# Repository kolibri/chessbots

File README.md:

# Chessbots

## What is this about?

You probably have seen something like this:

My idea is, to make the pieces movable. You play a game on your mobile phone or any other device that has a webbrowser, and the real pieces on the street will also make every move you and your opponent will make.

So, we are talking about 32 individual robots, each one is a selfmoving chesspiece, that play our game.

## Concept, Idea

Each piece is build with a ESP32-CAM board with two wheel attached, camera facing down. So we talk about a robot, that takes a picture of what is under it.
Hopefully, this is the board, that we play on. Because, this will have special markings, that help us to determine the position of the bot and where it is heading at.
Because, if we know that, we can check all the positions against an ongoing chess game, and so on.
This is the first main goals: Make the bots recognize its position and make it able to move to another position.

This is a very early project state. And it is slow moving. 

You may contact me (have a look at my github profile, or leave an issue), if you are interested in this project or want to contribute. There are plenty of issues, that are not solved yet. (languages I understand: german and english)

## Languages

Python (Flask), Micropython, ReactJs for Debug Frontend

Docker for dev env

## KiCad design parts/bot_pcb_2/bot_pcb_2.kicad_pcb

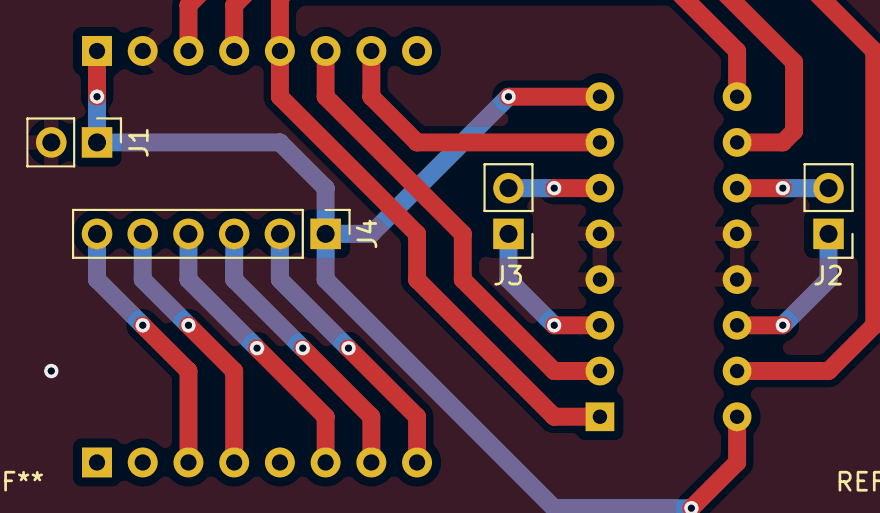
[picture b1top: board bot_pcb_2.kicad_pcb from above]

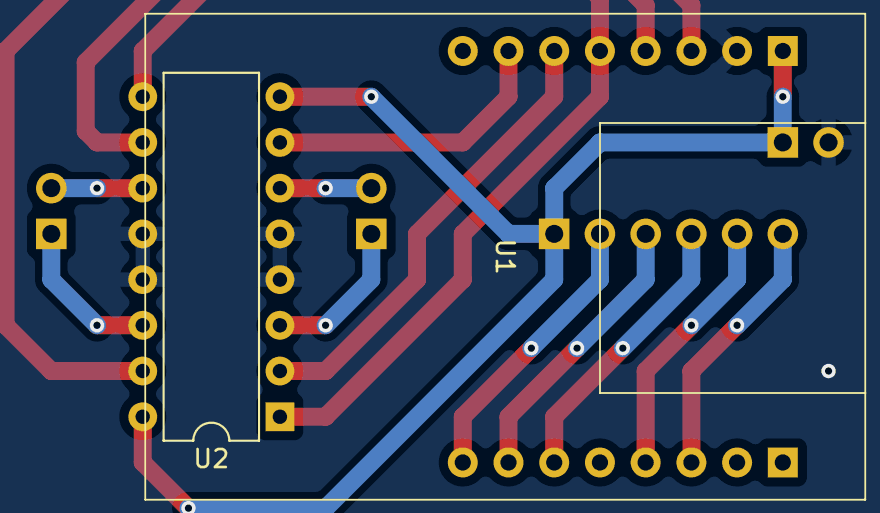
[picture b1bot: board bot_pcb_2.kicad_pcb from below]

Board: 2 copper layers, 6 parts (2 on the bottom side), 16 nets.

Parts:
J1, J2, J3: Conn_01x02_Pin; PinHeader_1x02_P2.54mm_Vertical
J4: Conn_01x06; PinHeader_1x06_P2.54mm_Vertical
U1: ESP32-CAM
U2: L293D; DIP-16_W7.62mm

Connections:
unnamed: J1.1, J4.1, U1.8 (5V), U2.8 (VCC2), U2.16 (VCC1)
unnamed: J1.2, U1.7 (GND_1), U2.4 (GND), U2.5 (GND), U2.12 (GND), U2.13 (GND)
unnamed: J2.1, U2.14 (4Y)
unnamed: J2.2, U2.11 (3Y)
unnamed: J3.1, U2.3 (1Y)
unnamed: J3.2, U2.6 (2Y)
unnamed: J4.2, U1.16 (GND_3)
unnamed: J4.3, U1.15 (U0T)
unnamed: J4.4, U1.14 (U0R)
unnamed: J4.5, U1.12 (GND_2)
unnamed: J4.6, U1.11 (IO0)
unnamed: U1.2 (IO2), U2.7 (2A)
unnamed: U1.6 (IO12), U2.15 (4A)
unnamed: U1.5 (IO13), U2.10 (3A)
unnamed: U1.3 (IO14), U2.2 (1A)
unnamed: U1.4 (IO15), U2.1 (EN1,2), U2.9 (EN3,4)

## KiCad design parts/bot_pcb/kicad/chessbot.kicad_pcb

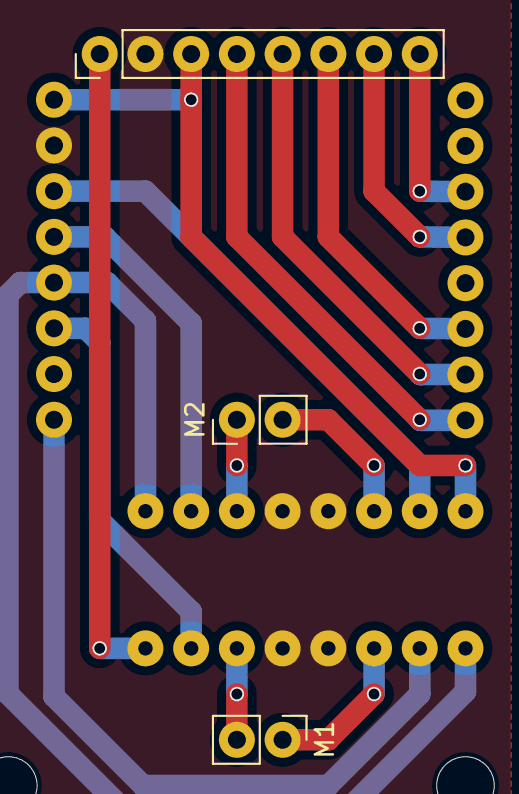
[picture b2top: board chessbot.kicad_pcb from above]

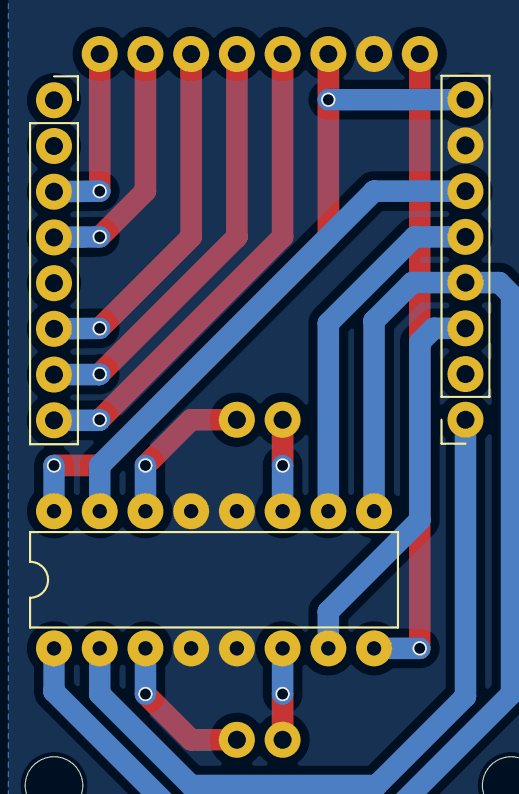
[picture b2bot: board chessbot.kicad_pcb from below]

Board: 2 copper layers, 10 parts (3 on the bottom side), 17 nets.

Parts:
Conn_ESP1, Conn_ESP2: Conn_01x08_Socket; PinSocket_1x08_P2.54mm_Vertical
H1, H2, H3, H4: MountingHole; MountingHole_3.2mm_M3
L293D1: L293D; DIP-16_W7.62mm
M1, M2: Conn_01x02_Pin; PinHeader_1x02_P2.54mm_Vertical
VCC_Flash1: Conn_01x08_Pin; PinHeader_1x08_P2.54mm_Vertical

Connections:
GND: Conn_ESP2.7, L293D1.4 (GND), L293D1.5 (GND), L293D1.12 (GND), L293D1.13 (GND), VCC_Flash1.2
unnamed: Conn_ESP2.8, L293D1.16 (VCC1), VCC_Flash1.3
unnamed: L293D1.8 (VCC2), VCC_Flash1.1
unnamed: Conn_ESP1.3, VCC_Flash1.8
unnamed: Conn_ESP1.4, VCC_Flash1.7
unnamed: Conn_ESP1.6, VCC_Flash1.6
unnamed: Conn_ESP1.7, VCC_Flash1.5
unnamed: Conn_ESP1.8, VCC_Flash1.4
unnamed: Conn_ESP2.1, L293D1.2 (1A)
unnamed: Conn_ESP2.3, L293D1.7 (2A)
unnamed: Conn_ESP2.4, L293D1.1 (EN1,2), L293D1.9 (EN3,4)
unnamed: Conn_ESP2.5, L293D1.10 (3A)
unnamed: Conn_ESP2.6, L293D1.15 (4A)
unnamed: L293D1.3 (1Y), M1.1
unnamed: L293D1.6 (2Y), M1.2
unnamed: L293D1.11 (3Y), M2.1
unnamed: L293D1.14 (4Y), M2.2

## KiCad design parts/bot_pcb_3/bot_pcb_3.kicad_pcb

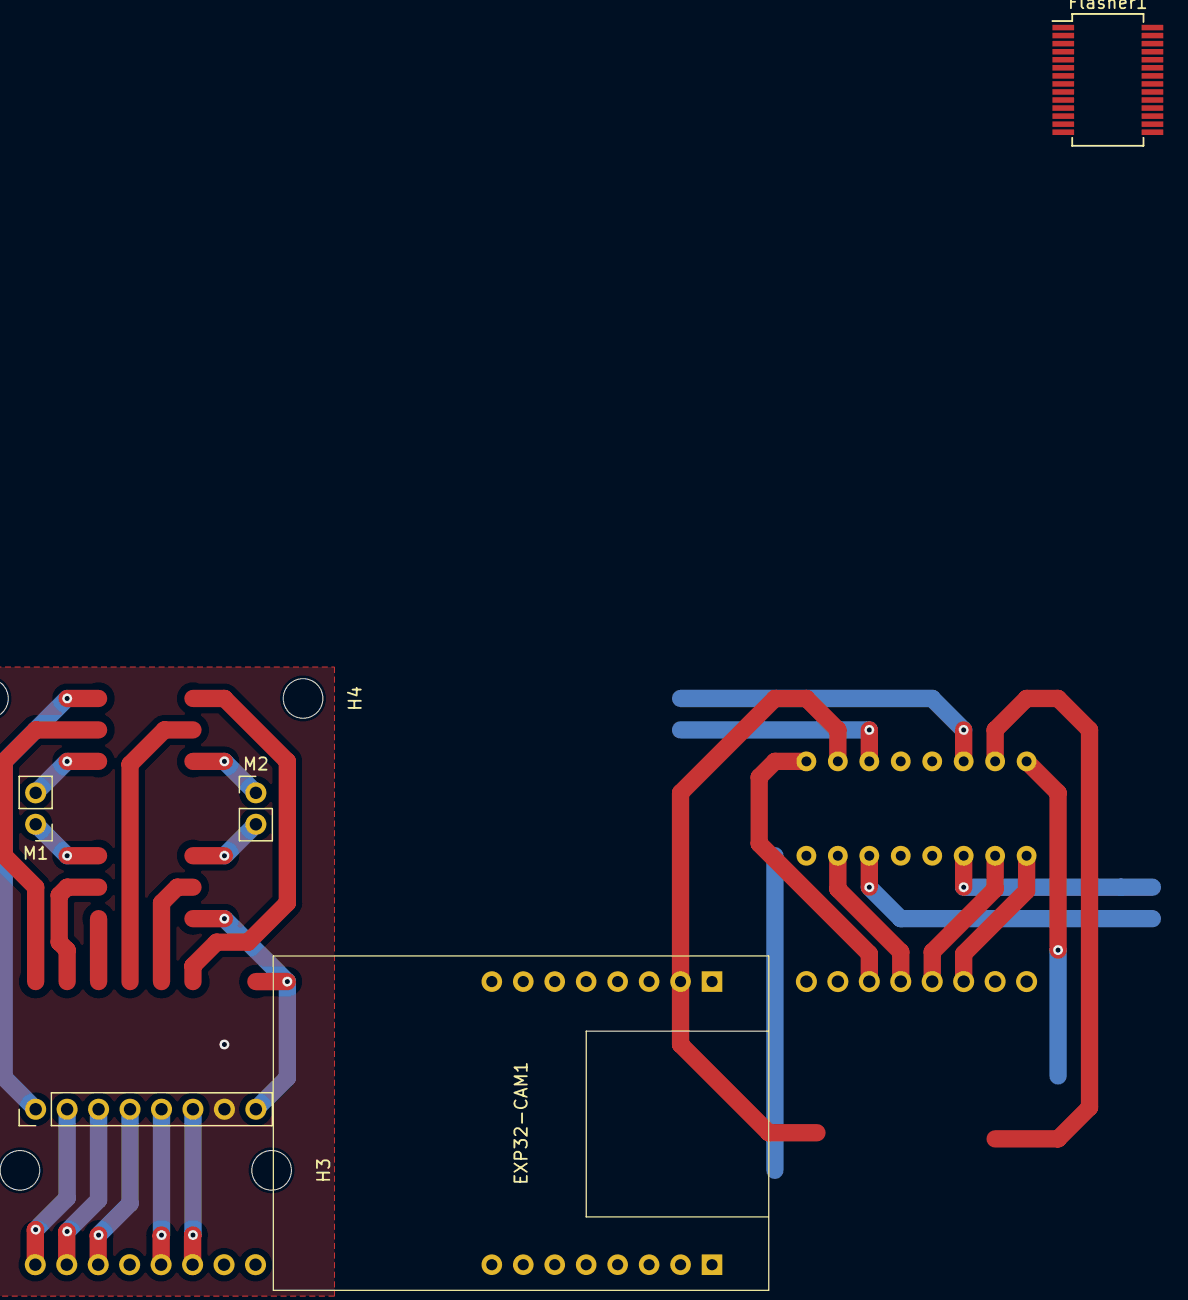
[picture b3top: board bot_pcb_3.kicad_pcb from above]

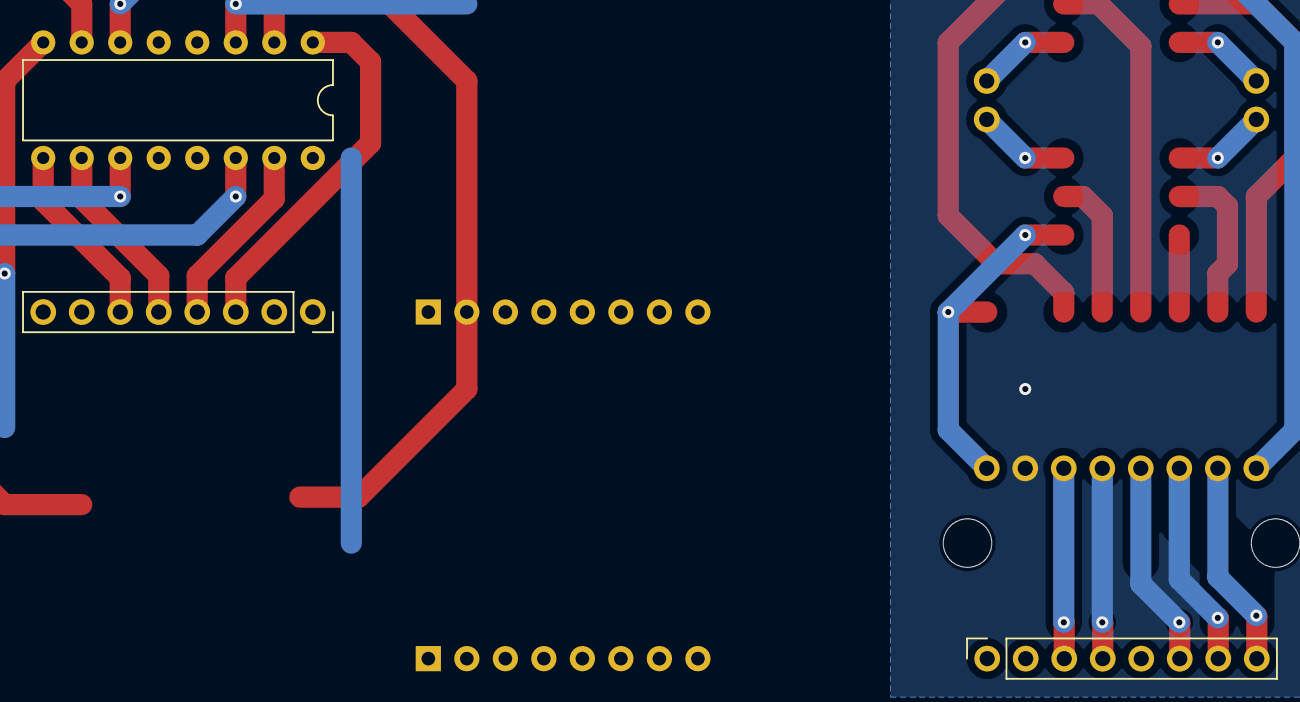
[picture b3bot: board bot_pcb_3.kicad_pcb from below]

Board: 2 copper layers, 12 parts (3 on the bottom side), 18 nets.

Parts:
Conn_ESP1, Conn_ESP2: Conn_01x08_Socket; PinSocket_1x08_P2.54mm_Vertical
EXP32-CAM1: ESP32-CAM
Flasher1: FT232RL; SSOP-28_5.3x10.2mm_P0.65mm
H1, H2, H3, H4: MountingHole; MountingHole_3.2mm_M3
L293D1: L293D; DIP-16_W7.62mm
M1, M2: Conn_01x02_Pin; PinHeader_1x02_P2.54mm_Vertical
VCC_Flash1: Conn_01x08_Pin; PinHeader_1x08_P2.54mm_Vertical

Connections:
GND: Conn_ESP2.7, EXP32-CAM1.7 (GND_1), Flasher1.21 (GND), L293D1.4 (GND), L293D1.5 (GND), L293D1.12 (GND), L293D1.13 (GND), VCC_Flash1.7
unnamed: Conn_ESP2.8, EXP32-CAM1.8 (5V), Flasher1.20 (VCC), L293D1.16 (VCC1), VCC_Flash1.8
unnamed: L293D1.8 (VCC2), VCC_Flash1.1
unnamed: Conn_ESP1.3, EXP32-CAM1.11 (IO0), VCC_Flash1.6
unnamed: Conn_ESP1.4, EXP32-CAM1.12 (GND_2), VCC_Flash1.5
unnamed: Conn_ESP1.6, EXP32-CAM1.14 (U0R), Flasher1.1 (TXD), VCC_Flash1.4
unnamed: Conn_ESP1.7, EXP32-CAM1.15 (U0T), Flasher1.5 (RXD), VCC_Flash1.3
unnamed: Conn_ESP1.8, EXP32-CAM1.16 (GND_3), VCC_Flash1.2
unnamed: Conn_ESP2.1, EXP32-CAM1.1 (IO4), L293D1.7 (2A)
unnamed: Conn_ESP2.2, EXP32-CAM1.2 (IO2), L293D1.2 (1A)
unnamed: Conn_ESP2.3, EXP32-CAM1.3 (IO14), L293D1.1 (EN1,2)
unnamed: Conn_ESP2.4, EXP32-CAM1.4 (IO15), L293D1.15 (4A)
unnamed: Conn_ESP2.5, EXP32-CAM1.5 (IO13), L293D1.10 (3A)
unnamed: Conn_ESP2.6, EXP32-CAM1.6 (IO12), L293D1.9 (EN3,4)
unnamed: L293D1.3 (1Y), M1.1
unnamed: L293D1.6 (2Y), M1.2
unnamed: L293D1.11 (3Y), M2.1
unnamed: L293D1.14 (4Y), M2.2

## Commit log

2018-07-26 Inital commit
2018-07-26 First test moving wires
2018-08-05 removed node modules from git
2018-08-05 Soldered motor controls and some research about nfc
2018-08-05 Some readme
2018-08-05 devblog restructure
2018-08-20 readme
2018-08-20 esp8266 prototype sketch and fritzings
2018-08-21 working arduino prototype lvl 1
2018-08-21 working react prototype
2018-09-05 Added bot sketch
2018-09-05 Fix bot sketch
2018-09-08 moving forward / backward
2018-09-08 bot prototype2
2018-09-09 cleanup
2018-09-09 sending rfid tags when scanned
2018-09-22 on the way to remove arduino ide
2018-09-22 motor to class
2018-09-25 First queuing stuff
2018-09-25 send multiple sequences
2018-09-26 nfc states
2018-10-02 cleanup, file renaming
2018-12-02 add firtzing
2019-04-30 Added SequenceStuff?
2020-02-26 bot.ino contains working two rfid readers.
2020-03-11 Setup arduino-cli
2020-04-29 bootstrapping server app with symfony
2020-05-09 Registering at server
2020-05-09 Boostraped fetching tags from bot
2020-05-09 Added basic tag recieving handling in server
2020-05-10 WIP adding cardreader
2020-05-22 dotenv stuff
2020-05-22 Adding cardReader for switching pc
2022-04-18 opencv seems easy
2022-04-25 reboot with python flask
2022-04-30 cleanup and use docker for flask
2022-05-04 unfinished board print via pillow
2022-05-04 Cleanup board print generation
2022-05-25 some sort of rotation and grid detection
2022-06-17 fixes
2022-06-17 We can test now, whoo
2022-06-17 forward correct detection with testing. wheee
2022-06-17 added favicon
2022-06-18 pcb in fritzing
2022-06-26 _main.scad is now the entrypiont
2022-07-08 refactor dashboard js and css
2022-07-08 alos
2022-07-08 mockbots working after file format change
2022-07-08 image creation and stuff
2022-07-08 testing board finding matches
2022-07-08 removed server, its not the time now
2022-07-13 mv test
2022-08-15 kinda testet captchas
2022-08-20 Testing setup for finding marker points
2023-02-05 run.sh board run ubm - create test patterns for camera
2023-02-13 WIP mid refactor.
2023-03-09 dots to text
2023-03-09 mockbots to rule
2023-03-09 fix grid resolving
2023-03-09 Point and captcha detection
2023-03-11 WIP position detection
2023-03-19 all board detection with 360 rotation working o_O
2023-03-20 after working grid detection (again), now testing for position detectiong is set up
2023-03-22 Semi working position resolving
2023-03-24 cleanup things
2023-03-28 position detection with angle working. next: cleanup
2023-03-31 Board view prototype
2023-03-31 dashboard board view responsive
2023-04-01 WIP added react testapp, next: add bot register and update, inlcude into normal build
2023-04-01 css messy, but functional dashboard with react. next: detail view
2023-04-08 long time ago I committed...
2023-05-08 some working motor controls
2024-01-30 long time no commit, should be last commit including simple dc motors. next should be steppers
2024-01-30 cleanup for steppers

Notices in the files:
README.md:
Creative Commons BY NC SA
